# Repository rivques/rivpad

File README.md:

# rivpad
a [hackpad](https://hackpad.hackclub.com) macropad. designed to be a system monitor so i can tell if the program that's hanging in my terminal is actually doing something or not

## features
- 9 keys
- OLED display
- 16 RGB LEDs, intended as system monitors
- PCB-mount style, no top plate
- optional USB port for daisy chaining keyboards

## demo link
[demo](https://youtube.com/shorts/DjA1d4YHZ9s?feature=share)

## cad
The CAD is in an Onshape document available [here](https://cad.onshape.com/documents/859a6718b395782d916274d9/w/acb2d55d003e03c3719d4ca6/e/6f143904c3132775702816f5?renderMode=0&uiState=6834dff6784e7633979328d8).

## a note on the custom firmware
because i want to use the RGB LEDs to monitor system load, i had to write custom firmware, because neither qmk nor kmk supports getting info from the host like that.

## a note on the usb port
the USB port is optional. it's intended to forward HID packets from a second keyboard using pico-pio-usb. because this would require even more custom firmware, i don't plan to do it immediately but did break out the required pins on the PCB.

## screenshots
### overall

### case

### schematic

### pcb

| Quantity | Item                       | Source                                                                                     | Optional |
|----------|----------------------------|--------------------------------------------------------------------------------------------|----------|
| 1        | XIAO RP2040                | [hackpad kit](https://hackpad.hackclub.com/parts)                                         | No       |
| 16       | SK6812MINI-E RGB LEDs      | [hackpad kit](https://hackpad.hackclub.com/parts)                                         | No       |
| 9        | Cherry MX-style switches   | [hackpad kit](https://hackpad.hackclub.com/parts)                                         | No       |
| 9        | 1N4148 diodes              | [hackpad kit](https://hackpad.hackclub.com/parts)                                         | No       |
| 1        | 0.91" OLED display         | [hackpad kit](https://hackpad.hackclub.com/parts)                                         | No       |
| 2        | 4.7kΩ resistors            | [hackpad kit](https://hackpad.hackclub.com/parts)                                         | No       |
| 9        | DSA keycaps                | [hackpad kit](https://hackpad.hackclub.com/parts)                                         | No       |
| 1        | 3D-printed case            | [hackpad kit](https://hackpad.hackclub.com/parts)                                         | No       |
| 1        | PCB                        | [jlcpcb.com](https://jlcpcb.com)                                                          | No       |
| 4        | M3x10mm bolts              | [hackpad kit](https://hackpad.hackclub.com/parts)                                         | No       |
| 4        | M3 heat-set inserts        | [hackpad kit](https://hackpad.hackclub.com/parts)                                         | No       |
| 4        | Anti-slip rubber feet      | [these](https://www.adafruit.com/product/550)                                             | Yes      |
| 1        | USB-A female connector     | [this](https://www.digikey.com/en/products/detail/on-shore-technology-inc/USB-A1HSW6/2677750) | Yes      |

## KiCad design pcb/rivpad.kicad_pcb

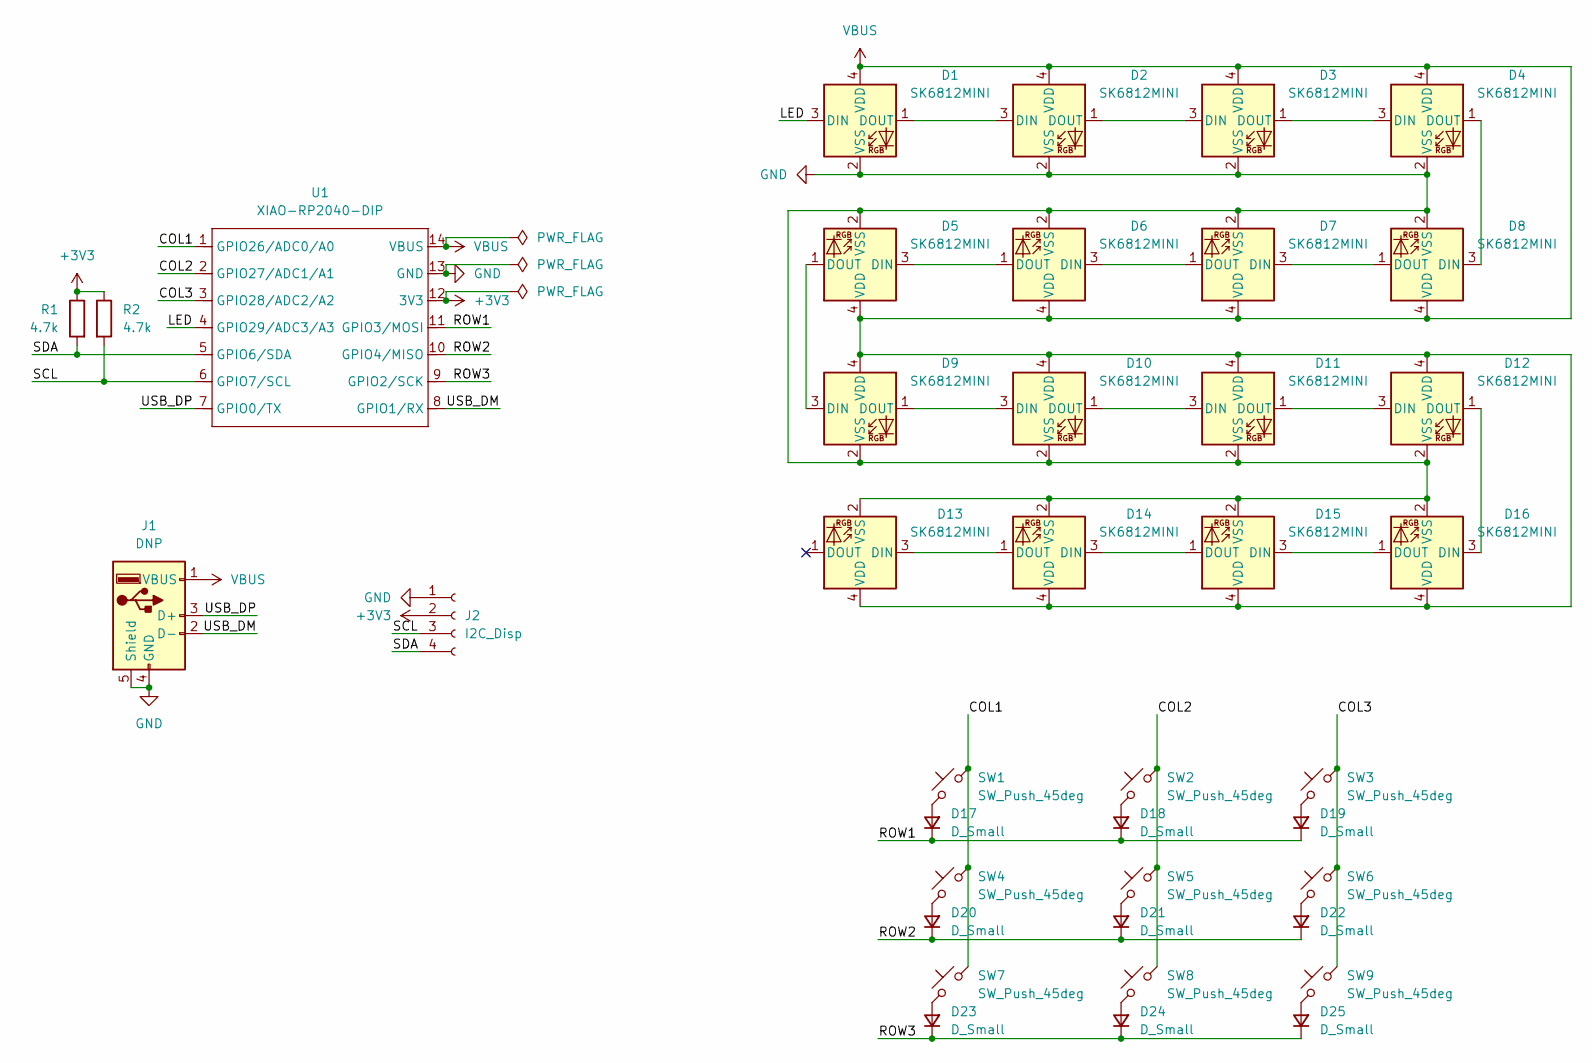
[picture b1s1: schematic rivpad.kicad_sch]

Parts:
D1, D2, D3, D4, D5, D6, D7, D8, D9, D10, D11, D12, D13, D14, D15, D16: SK6812MINI; SK6812-MINI-E
D17, D18, D19, D20, D21, D22, D23, D24, D25: D_Small; D_DO-35_SOD27_P7.62mm_Horizontal
J1: DNP; USB_A_Connfly_DS1095
J2: I2C_Disp; PinHeader_1x04_P2.54mm_Vertical
R1, R2: 4.7k; R_Axial_DIN0207_L6.3mm_D2.5mm_P7.62mm_Horizontal
SW1, SW2, SW3, SW4, SW5, SW6, SW7, SW8, SW9: SW_Push_45deg; SW_Cherry_MX_1.00u_PCB
U1: XIAO-RP2040-DIP

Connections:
+3V3: J2.2, R1.1, R2.1, U1.12 (3V3)
/COL1: SW1.2, SW4.2, SW7.2, U1.1 (GPIO26/ADC0/A0)
/COL2: SW2.2, SW5.2, SW8.2, U1.2 (GPIO27/ADC1/A1)
/COL3: SW3.2, SW6.2, SW9.2, U1.3 (GPIO28/ADC2/A2)
/LED: D1.3 (DIN), U1.4 (GPIO29/ADC3/A3)
/ROW1: D17.1 (K), D18.1 (K), D19.1 (K), U1.11 (GPIO3/MOSI)
/ROW2: D20.1 (K), D21.1 (K), D22.1 (K), U1.10 (GPIO4/MISO)
/ROW3: D23.1 (K), D24.1 (K), D25.1 (K), U1.9 (GPIO2/SCK)
/SCL: J2.3, R2.2, U1.6 (GPIO7/SCL)
/SDA: J2.4, R1.2, U1.5 (GPIO6/SDA)
/USB_DM: J1.2 (D-), U1.8 (GPIO1/RX)
/USB_DP: J1.3 (D+), U1.7 (GPIO0/TX)
GND: D1.2 (VSS), D2.2 (VSS), D3.2 (VSS), D4.2 (VSS), D5.2 (VSS), D6.2 (VSS), D7.2 (VSS), D8.2 (VSS), D9.2 (VSS), D10.2 (VSS), D11.2 (VSS), D12.2 (VSS), D13.2 (VSS), D14.2 (VSS), D15.2 (VSS), D16.2 (VSS), J1.4 (GND), J1.5 (Shield), J2.1, U1.13 (GND)
unnamed: D1.1 (DOUT), D2.3 (DIN)
unnamed: D2.1 (DOUT), D3.3 (DIN)
unnamed: D3.1 (DOUT), D4.3 (DIN)
unnamed: D4.1 (DOUT), D8.3 (DIN)
unnamed: D5.3 (DIN), D6.1 (DOUT)
unnamed: D5.1 (DOUT), D9.3 (DIN)
unnamed: D6.3 (DIN), D7.1 (DOUT)
unnamed: D7.3 (DIN), D8.1 (DOUT)
unnamed: D9.1 (DOUT), D10.3 (DIN)
unnamed: D10.1 (DOUT), D11.3 (DIN)
unnamed: D11.1 (DOUT), D12.3 (DIN)
unnamed: D12.1 (DOUT), D16.3 (DIN)
unnamed: D13.3 (DIN), D14.1 (DOUT)
unnamed: D14.3 (DIN), D15.1 (DOUT)
unnamed: D15.3 (DIN), D16.1 (DOUT)
unnamed: D17.2 (A), SW1.1
unnamed: D18.2 (A), SW2.1
unnamed: D19.2 (A), SW3.1
unnamed: D20.2 (A), SW4.1
unnamed: D21.2 (A), SW5.1
unnamed: D22.2 (A), SW6.1
unnamed: D23.2 (A), SW7.1
unnamed: D24.2 (A), SW8.1
unnamed: D25.2 (A), SW9.1
VBUS: D1.4 (VDD), D2.4 (VDD), D3.4 (VDD), D4.4 (VDD), D5.4 (VDD), D6.4 (VDD), D7.4 (VDD), D8.4 (VDD), D9.4 (VDD), D10.4 (VDD), D11.4 (VDD), D12.4 (VDD), D13.4 (VDD), D14.4 (VDD), D15.4 (VDD), D16.4 (VDD), J1.1 (VBUS), U1.14 (VBUS)

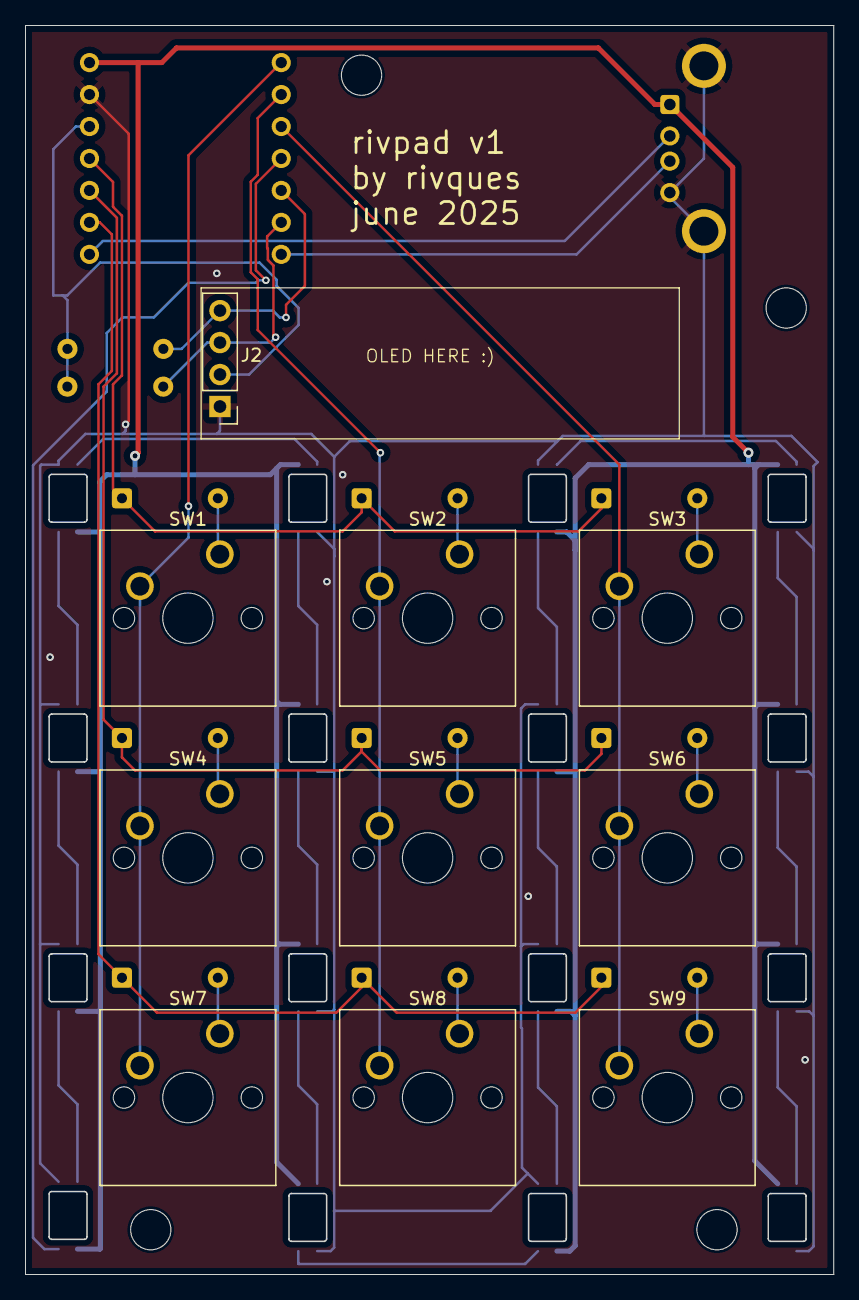
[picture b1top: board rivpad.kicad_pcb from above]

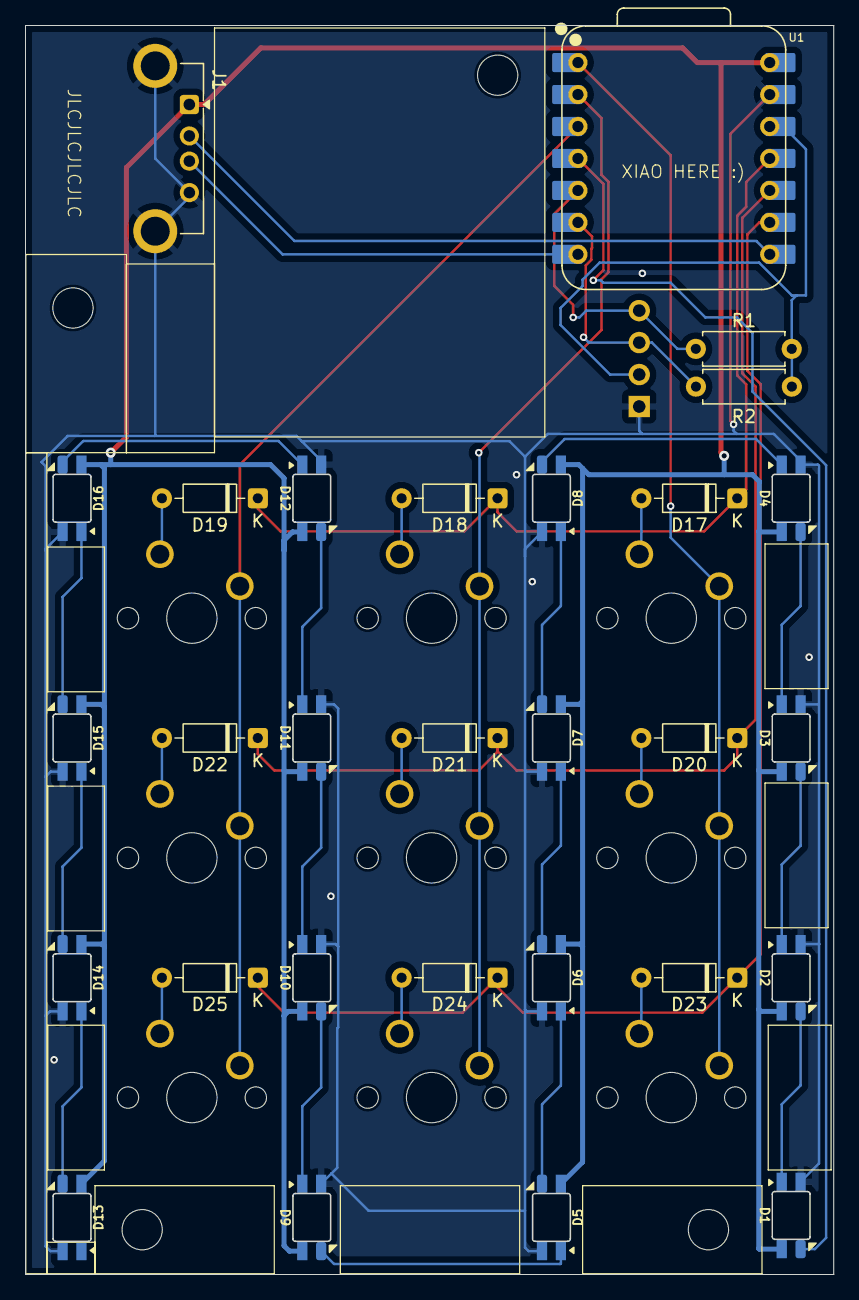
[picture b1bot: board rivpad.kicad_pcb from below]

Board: 2 copper layers, 64.2 x 99.2 mm, 39 parts (29 on the bottom side), 38 nets.

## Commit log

2025-05-26 add gitignore
2025-05-26 make pcb!
2025-05-26 add mounting holes to board and adjust readme
2025-05-26 add case cad
2025-05-27 add custom firmware
2025-05-27 get things in the right shape for submission
2025-05-27 add images to readme
2025-06-23 make the real thing work!
2025-06-24 fix a few bugs in the firmware
2025-07-05 make daemon pick higher-numbered port
